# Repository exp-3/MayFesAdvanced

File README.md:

# MayFesAdvanced
2016年度東京大学五月祭電子工作体験企画の上級編のレポジトリ
* 加速度センサを入力に用いており，ゲーム機を傾けて操作します．
* ブロック崩し，棒を倒れないようにするゲーム，降ってくる障害物を避けるゲームが楽しめます．

## 完成図

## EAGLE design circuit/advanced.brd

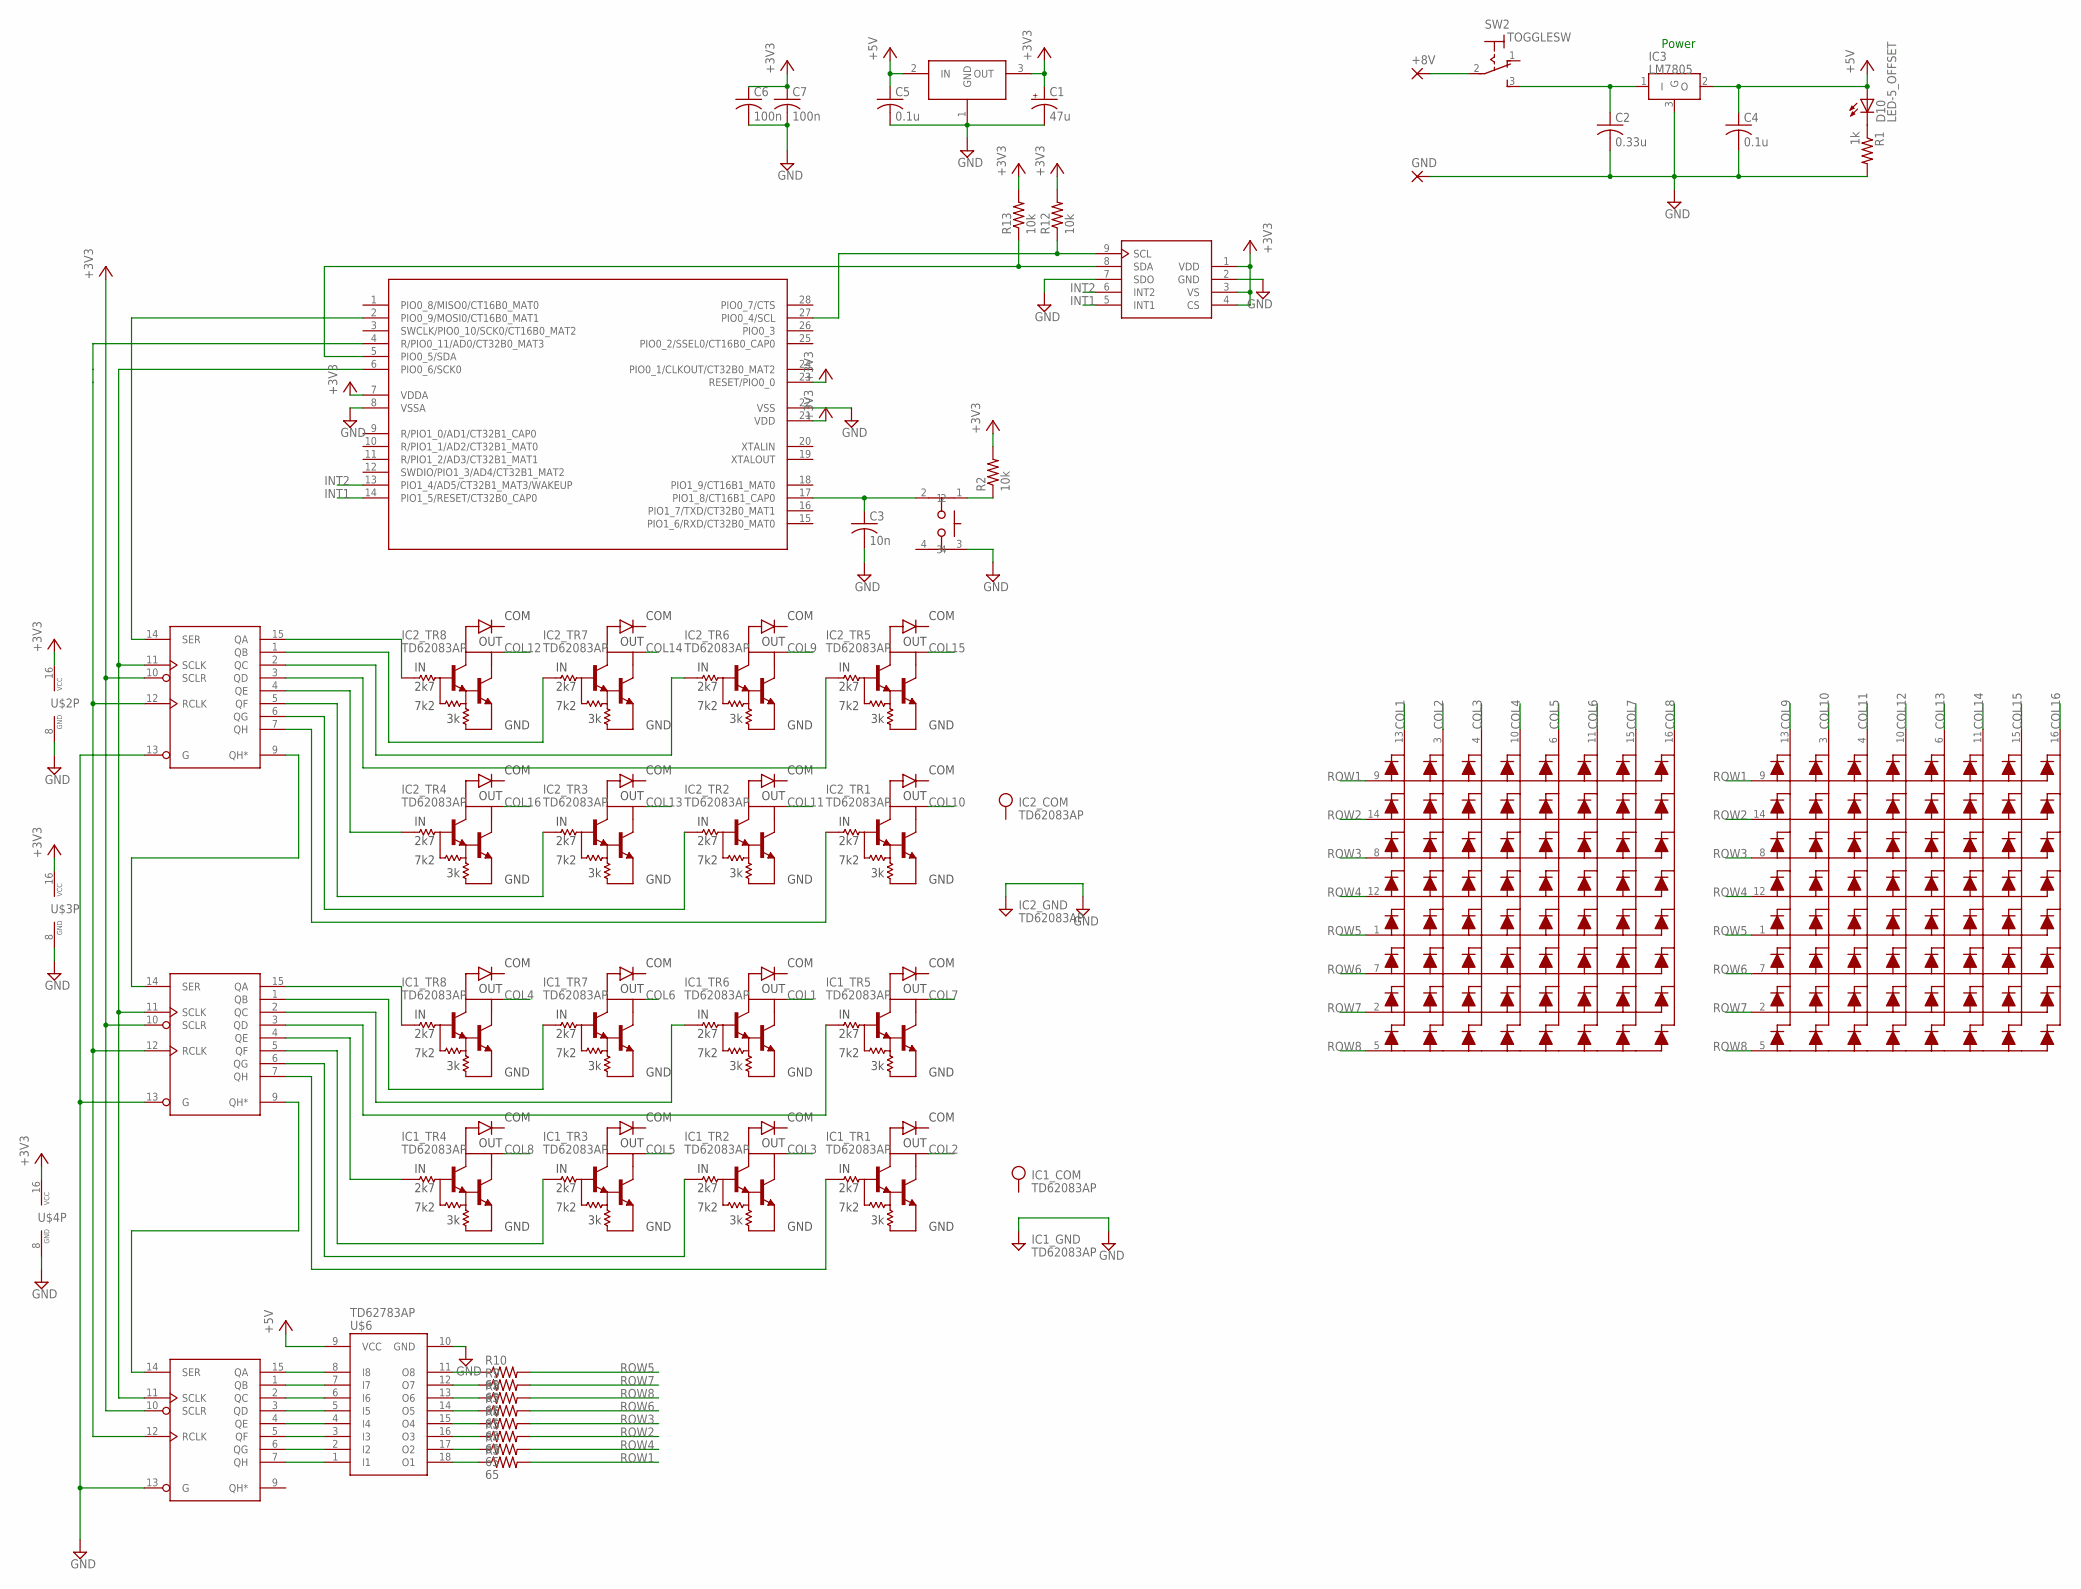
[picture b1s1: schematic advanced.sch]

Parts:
+8V: POWERPAD-2.0
C1: 47u; E2,5-5
C2: 0.33u; C025-024X044
C3: 10n; C025-024X044
C4, C5: 0.1u; C025-024X044
C6, C7: 100n; C025-024X044
D1: OSL641505-BX; OSL641505-XX
D10: LED-5_OFFSET; LED5_OFFSET
DELDEL: OSL641505-BX; OSL641505-XX
GND: POWERPAD-2.0
IC1, IC2: TD62083AP; DIL18
IC3: LM7805; 7805-LARGEHOLE
R1: 1k; 0204/7
R2, R12, R13: 10k; 0204/7
R3, R4, R5, R6, R7, R8, R9, R10: 65; 0204/7
SW1: PUSHSW
SW2: TOGGLESW
U$1: LPC1114FN28; DIP28(600MIL)
U$2, U$3, U$4: 74HC595N; DIL16
U$5: AKI_ADXL345
U$6: TD62783AP; DIL18
U$8: S-812C3.3AY; TO92-

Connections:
+3V3: C1.+, C6.1, C7.1, R2.2, R12.2, R13.2, U$1.7 (VDDA), U$1.21 (VDD), U$1.23 (RESET/PIO0_0), U$2.10 (SCLR), U$2.16 (VCC), U$3.10 (SCLR), U$3.16 (VCC), U$4.10 (SCLR), U$4.16 (VCC), U$5.1 (VDD), U$5.3 (VS), U$5.4 (CS), U$8.3 (OUT)
+5V: C4.1, C5.1, D10.A, IC3.2 (O), U$6.9 (VCC), U$8.2 (IN)
COL1: D1.13, IC1.13 (C)
COL2: D1.3, IC1.18 (C)
COL3: D1.4, IC1.17 (C)
COL4: D1.10, IC1.11 (C)
COL5: D1.6, IC1.16 (C)
COL6: D1.11, IC1.12 (C)
COL7: D1.15, IC1.14 (C)
COL8: D1.16, IC1.15 (C)
COL9: DELDEL.13, IC2.13 (C)
COL10: DELDEL.3, IC2.18 (C)
COL11: DELDEL.4, IC2.17 (C)
COL12: DELDEL.10, IC2.11 (C)
COL13: DELDEL.6, IC2.16 (C)
COL14: DELDEL.11, IC2.12 (C)
COL15: DELDEL.15, IC2.14 (C)
COL16: DELDEL.16, IC2.15 (C)
GND: C1.-, C2.2, C3.2, C4.2, C5.2, C6.2, C7.2, GND.1, IC1.9 (GND), IC2.9 (GND), IC3.3 (G), R1.2, SW1.3, U$1.8 (VSSA), U$1.22 (VSS), U$2.8 (GND), U$2.13 (G), U$3.8 (GND), U$3.13 (G), U$4.8 (GND), U$4.13 (G), U$5.2 (GND), U$5.7 (SDO), U$6.10 (GND), U$8.1 (GND)
INT1: U$1.14 (PIO1_5/RESET/CT32B0_CAP0), U$5.5 (INT1)
INT2: U$1.13 (PIO1_4/AD5/CT32B1_MAT3/WAKEUP), U$5.6 (INT2)
unnamed: C3.1, SW1.2, U$1.17 (PIO1_8/CT16B1_CAP0)
unnamed: C2.1, IC3.1 (I), SW2.3 (S)
unnamed: U$2.14 (SER), U$3.9 (QH*)
unnamed: U$3.14 (SER), U$4.9 (QH*)
unnamed: U$2.15 (QA), U$6.8 (I8)
unnamed: +8V.1, SW2.2
unnamed: R12.1, U$1.27 (PIO0_4/SCL), U$5.9 (SCL)
unnamed: R13.1, U$1.5 (PIO0_5/SDA), U$5.8 (SDA)
unnamed: U$1.2 (PIO0_9/MOSI0/CT16B0_MAT1), U$4.14 (SER)
unnamed: R2.1, SW1.1
unnamed: U$1.4 (R/PIO0_11/AD0/CT32B0_MAT3), U$2.12 (RCLK), U$3.12 (RCLK), U$4.12 (RCLK)
unnamed: IC1.4 (B), U$3.4 (QE)
unnamed: IC2.8 (B), U$4.15 (QA)
unnamed: IC2.7 (B), U$4.1 (QB)
unnamed: IC2.6 (B), U$4.2 (QC)
unnamed: U$2.1 (QB), U$6.7 (I7)
unnamed: U$2.2 (QC), U$6.6 (I6)
unnamed: U$2.3 (QD), U$6.5 (I5)
unnamed: U$2.4 (QE), U$6.4 (I4)
unnamed: U$2.5 (QF), U$6.3 (I3)
unnamed: U$2.6 (QG), U$6.2 (I2)
unnamed: U$2.7 (QH), U$6.1 (I1)
unnamed: IC1.8 (B), U$3.15 (QA)
unnamed: IC1.7 (B), U$3.1 (QB)
unnamed: IC1.6 (B), U$3.2 (QC)
unnamed: IC1.5 (B), U$3.3 (QD)
unnamed: IC1.1 (B), U$3.7 (QH)
unnamed: IC1.2 (B), U$3.6 (QG)
unnamed: IC1.3 (B), U$3.5 (QF)
unnamed: IC2.5 (B), U$4.3 (QD)
unnamed: IC2.1 (B), U$4.7 (QH)
unnamed: IC2.2 (B), U$4.6 (QG)
unnamed: IC2.3 (B), U$4.5 (QF)
unnamed: U$1.6 (PIO0_6/SCK0), U$2.11 (SCLK), U$3.11 (SCLK), U$4.11 (SCLK)
unnamed: IC2.4 (B), U$4.4 (QE)
unnamed: R3.1, U$6.18 (O1)
unnamed: R4.1, U$6.17 (O2)
unnamed: R5.1, U$6.16 (O3)
unnamed: R6.1, U$6.15 (O4)
unnamed: R7.1, U$6.14 (O5)
unnamed: R8.1, U$6.13 (O6)
unnamed: R9.1, U$6.12 (O7)
unnamed: R10.1, U$6.11 (O8)
unnamed: D10.K, R1.1
ROW1: D1.9, DELDEL.9, R3.2
ROW2: D1.14, DELDEL.14, R5.2
ROW3: D1.8, DELDEL.8, R6.2
ROW4: D1.12, DELDEL.12, R4.2
ROW5: D1.1, DELDEL.1, R10.2
ROW6: D1.7, DELDEL.7, R7.2
ROW7: D1.2, DELDEL.2, R9.2
ROW8: D1.5, DELDEL.5, R8.2

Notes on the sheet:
Power

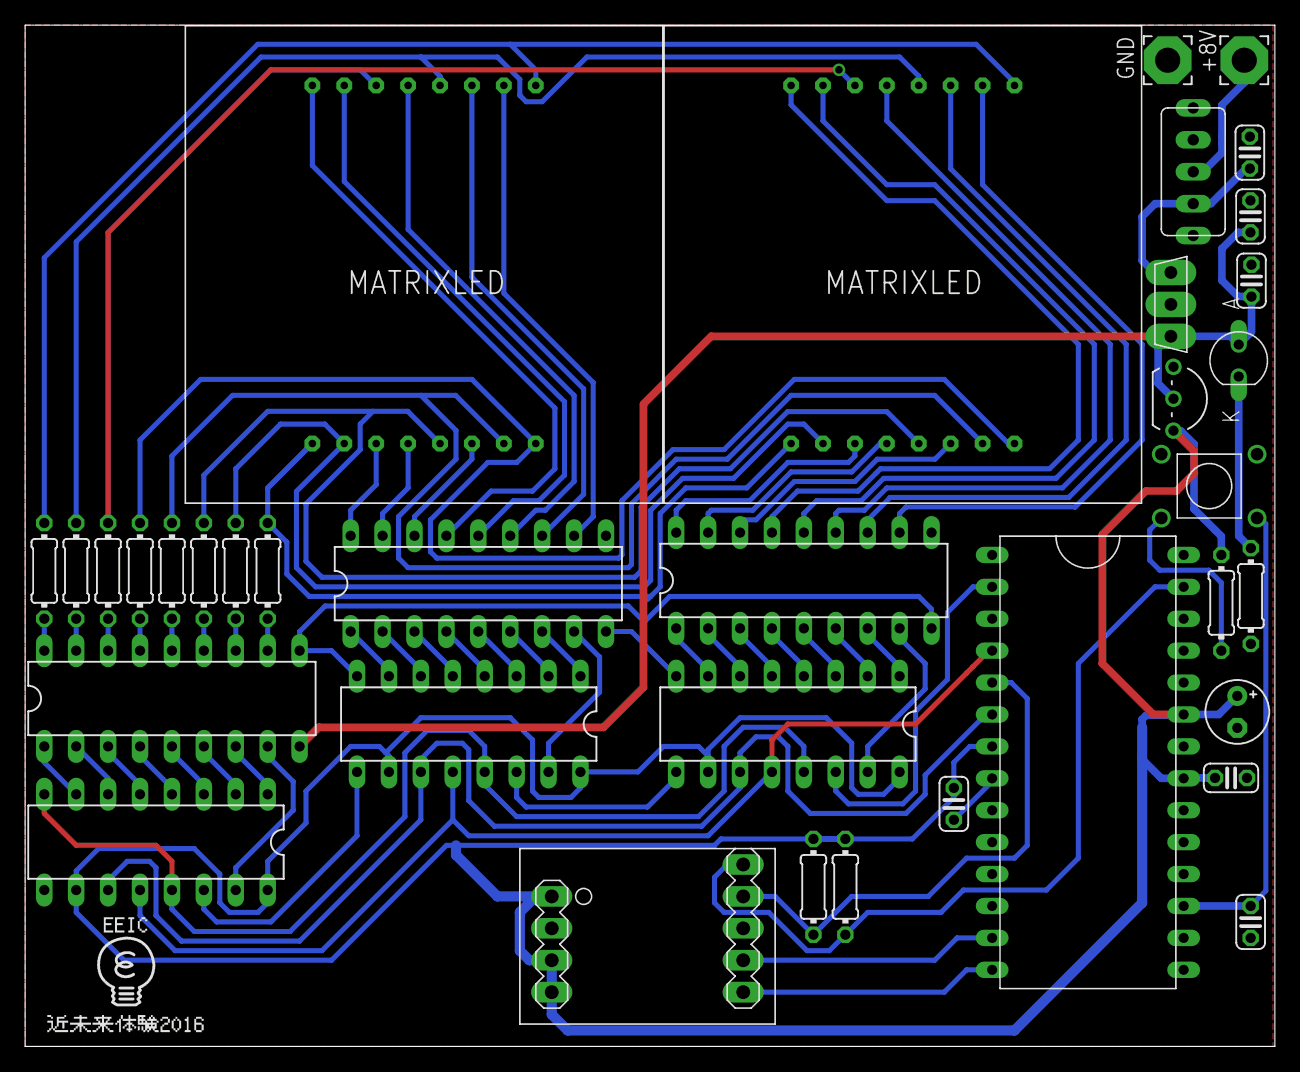
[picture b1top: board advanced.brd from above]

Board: 2 copper layers, 99.5 x 81.3 mm, 37 parts (0 on the bottom side), 73 nets.

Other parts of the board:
U$7: EEIC_LOGO

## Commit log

2016-03-25 makefileでsrc, inc以下のソースコードも取り込むようにした
2016-03-25 .gitcontrolの修正
2016-03-25 .clang_completeにincディレクトリを含めた
2016-03-25 displayのクラスを追加
2016-03-25 とりあえずmake通った
2016-03-25 ファイルの追加
2016-03-25 ヘッダファイルのインクルードガードの修正
2016-03-25 一通り実装
2016-03-25 bagfix
2016-03-26 初期化の時にバッファをクリアするようにした
2016-03-26 静的コンストメンバ変数の初期化場所をヘッダファイル内に移した
2016-03-26 タイマー割り込みを実装
2016-03-26 bug fix
2016-03-26 関数名の修正
2016-03-26 行ではなく列でダイナミック点灯するようにした
2016-03-26 加速度センサの値のキャストのバグの修正
2016-03-26 ledの周波数の修正
2016-03-27 ゲーム部分がひとまず完成
2016-03-27 modify dotfiles
2016-04-09 とりあえずspiを実装してみたが、まだ挙動がおかしい
2016-04-09 makefileの修正
2016-04-09 makefileと.gitignoreの修正
2016-04-09 folder構造の整理
2016-04-11 .gcc-flagsの修正
2016-04-11 インターフェースの定義
2016-04-11 ブロック崩しの実装
2016-04-29 mainファイルの改行コードの修正
2016-05-03 バッファからシフトレジスタ用のコードに変換するタイミングを変更した
2016-05-04 黒魔術によってチラツキが抑えられた (非常に謎)
2016-05-07 charactorクラスの実装
2016-05-12 KeepStickのゲームを追加した
2016-05-12 ふにゃふにゃ棒倒しゲームを完成させた
2016-05-13 remove Charactor class
2016-05-13 create Alphabets class
2016-05-13 add PushSwitch class
2016-05-13 implement pushswitch class
2016-05-13 pushswitch が読めるようになった
2016-05-13 KeepStickゲームのパラメーターを変えた
2016-05-13 Irairaゲームを追加した
2016-05-13 インターフェースにinit関数を追加した
2016-05-13 init関数を実装した
2016-05-13 irairaのinit関数を実装した
2016-05-13 keepstickのinit関数を実装した
2016-05-13 displayのset, reset関数で入力座標の領域内チェックを行うようにした
2016-05-13 openingの描画を実装した
2016-05-13 状態遷移を記述した
2016-05-13 ひとまず完成
2016-05-13 樋口のゲーム二種のパラメーターを変更した
2016-05-13 ゲームバランスの調整
2016-05-13 完成!!!!!!!!!!!!!!!!!!!!!!!!!!!!!!! やったね！ひぐちゃん！
2017-01-28 Create LICENSE
2017-01-28 回路図を追加した
2017-01-28 LICENSE, READMEの追加
2017-01-28 ディレクトリ構造の変更
2017-01-28 READMEを変更
2017-01-28 完成写真の追加
